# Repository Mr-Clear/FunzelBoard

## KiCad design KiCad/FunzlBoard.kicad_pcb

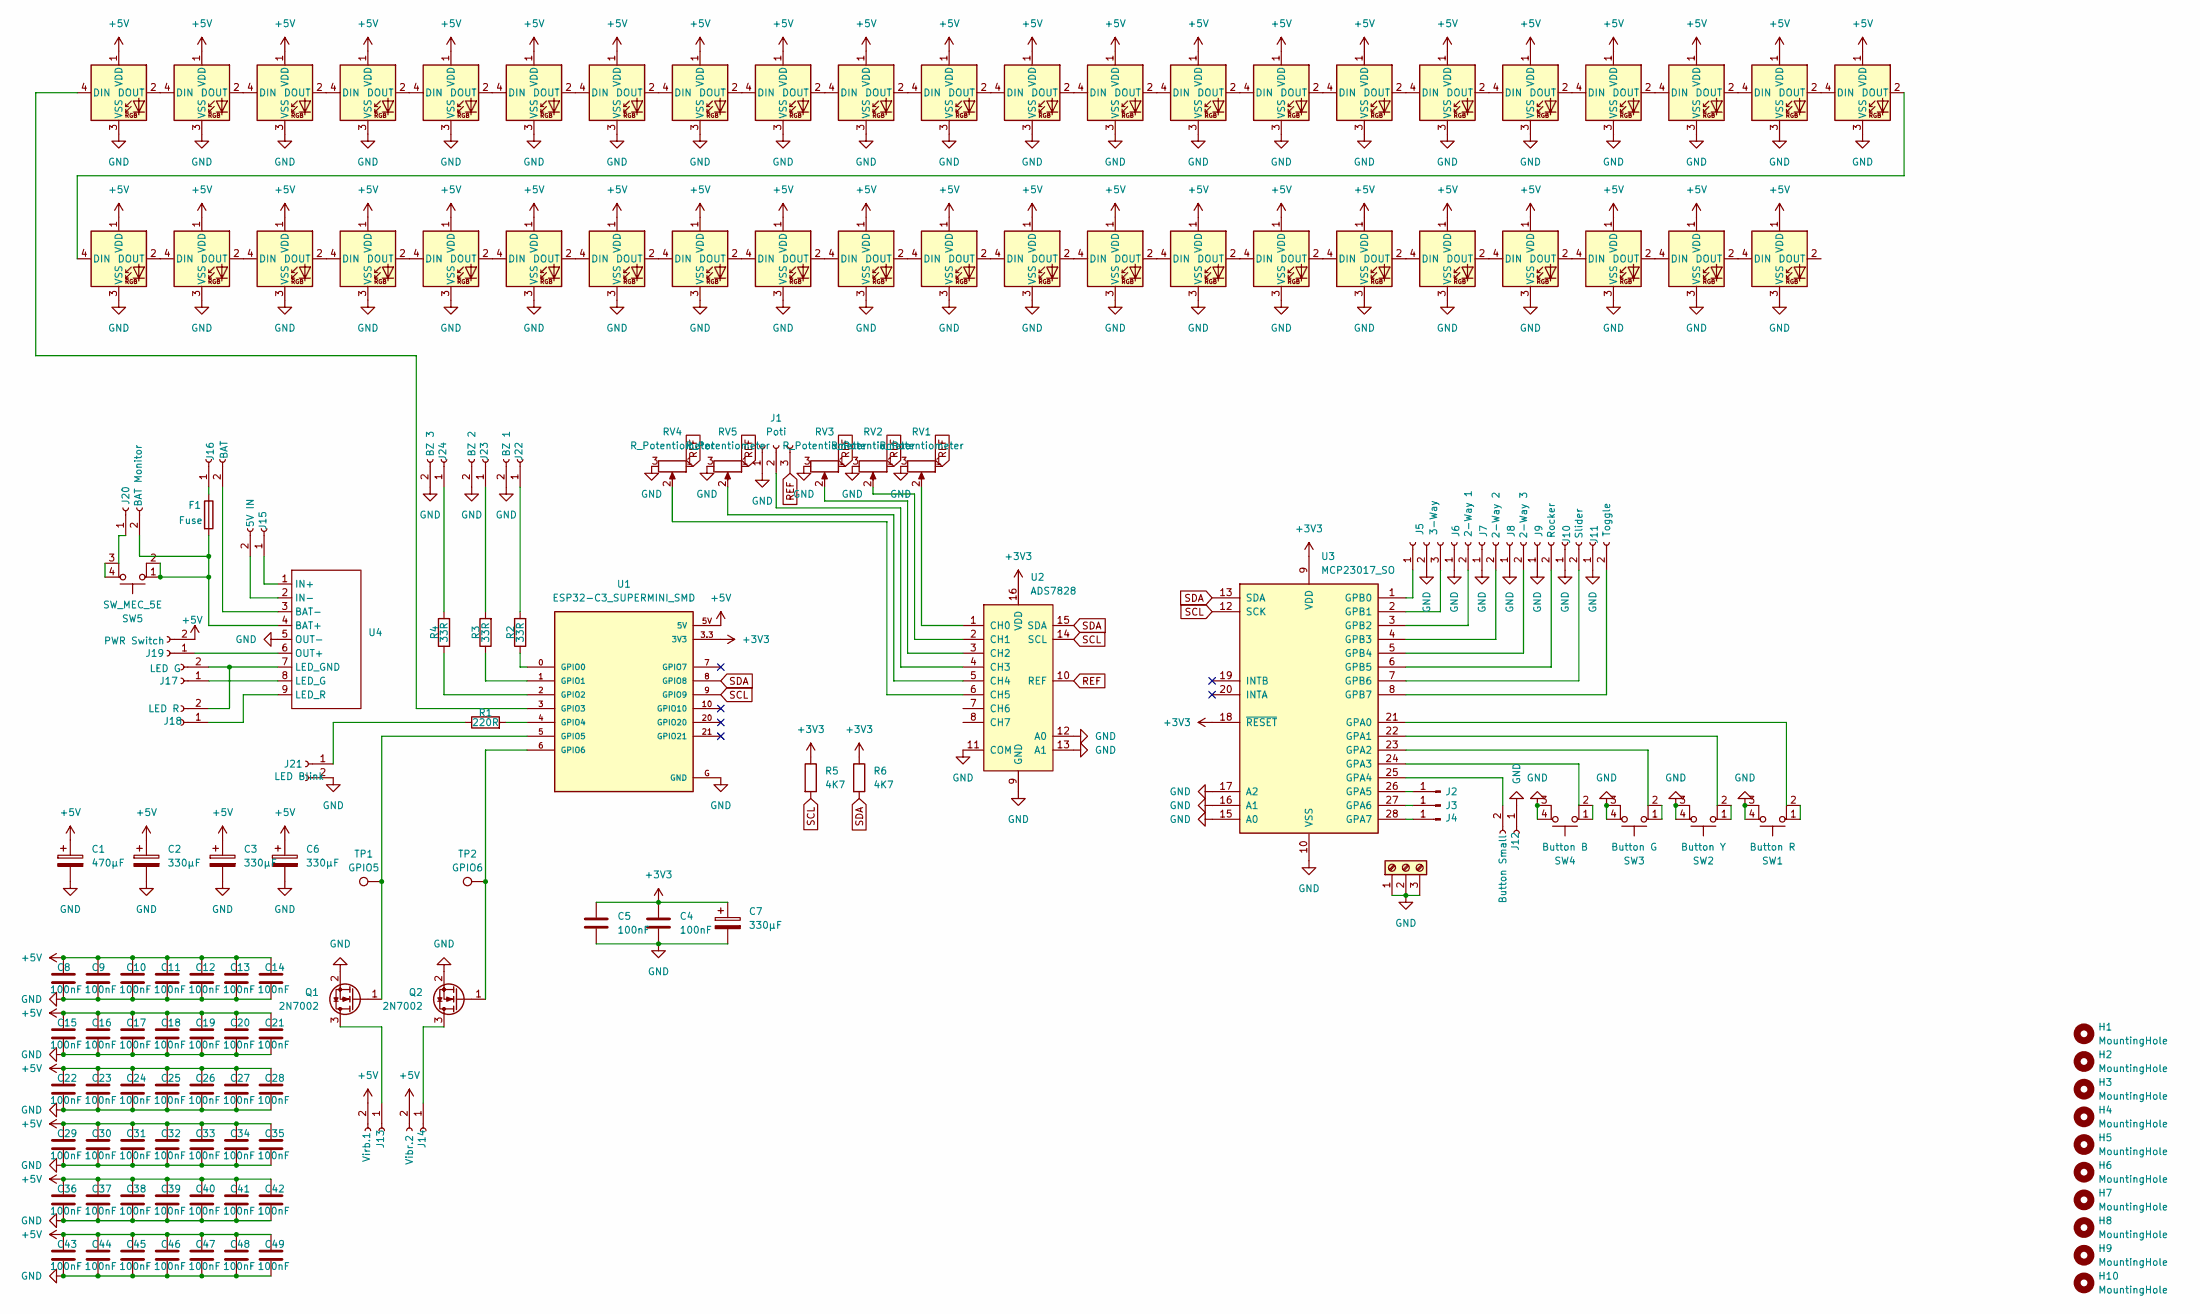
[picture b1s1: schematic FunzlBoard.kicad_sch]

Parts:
1WI1: Banana Plug Cable; TerminalBlock_Phoenix_MPT-0,5-3-2.54_1x03_P2.54mm_Horizontal
C1: 470µF; CP_Radial_D6.3mm_P2.50mm
C2, C3, C6, C7: 330µF; CP_Radial_D6.3mm_P2.50mm
C4, C5, C8, C9, C10, C11, C12, C13, C14, C15, C16, C17, C18, C19, C20, C21, C22, C23, C24, C25, C26, C27, C28, C29, C30, C31, C32, C33, C34, C35, C36, C37, C38, C39, C40, C41, C42, C43, C44, C45, C46, C47, C48, C49: 100nF; C_1206_3216Metric
D1, D2, D3, D4, D5, D6, D7, D8, D9, D10, D11, D12, D13, D14, D15, D16, D17, D18, D19, D20, D21, D22, D23, D24, D25, D26, D27, D28, D29, D30, D31, D32, D33, D34, D35, D36, D37, D38, D39, D40, D41, D42, D43: WS2812B; LED_WS2812B_PLCC4_5.0x5.0mm_P3.2mm
F1: Fuse; Fuseholder_Clip-5x20mm_Littelfuse_111_Inline_P20.00x5.00mm_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
H1, H2, H3, H4, H5, H6, H7, H8, H9, H10: MountingHole; MountingHole_4.3mm_M4_DIN965
J1: Poti; Connector3
J2: Banana Plug Socket 1; PinHeader_1x01_P2.54mm_Horizontal
J3: Banana Plug Socket 2; PinHeader_1x01_P2.54mm_Horizontal
J4: Banana Plug Socket 3; PinHeader_1x01_P2.54mm_Horizontal
J5: 3-Way; Connector3
J6: 2-Way 1; Connector2
J7: 2-Way 2; Connector2
J8: 2-Way 3; Connector2
J9: Rocker; Connector2
J10: Slider; Connector2
J11: Toggle; Connector2
J12: Button Small; Connector2
J13: Virb.1; Connector2
J14: Vibr.2; Connector2
J15: 5V IN; Connector2
J16: BAT; Connector2
J17: LED G; Connector2
J18: LED R; Connector2
J19: PWR Switch; Connector2
J20: BAT Monitor; Connector2
J21: LED Blink; Connector2
J22: BZ 1; Connector2
J23: BZ 2; Connector2
J24: BZ 3; Connector2
Q1, Q2: 2N7002; SOT-23
R1: 220R; R_1206_3216Metric
R2, R3, R4: 33R; R_1206_3216Metric
R5, R6: 4K7; R_1206_3216Metric
RV1, RV2, RV3: R_Potentiometer; Slider
RV4, RV5: R_Potentiometer; TrimmerH
SW1: Button R; ColorButton
SW2: Button Y; ColorButton
SW3: Button G; ColorButton
SW4: Button B; ColorButton
SW5: SW_MEC_5E; SW_PUSH_6mm_H13mm
TP1: GPIO5; TestPoint_THTPad_D1.5mm_Drill0.7mm
TP2: GPIO6; TestPoint_THTPad_D1.5mm_Drill0.7mm
U1: ESP32-C3_SUPERMINI_SMD; MODULE_ESP32-C3_SUPERMINI
U2: ADS7828; TSSOP-16_4.4x5mm_P0.65mm
U3: MCP23017_SO; SOIC-28W_7.5x17.9mm_P1.27mm
U4: Battery_Management

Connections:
+3V3: C4.1, C5.1, C7.1, R5.1, R6.1, U1.3.3 (3V3), U2.16 (VDD), U3.9 (VDD), U3.18 (~RESET)
+5V: C1.1, C2.1, C3.1, C6.1, C8.1, C9.1, C10.1, C11.1, C12.1, C13.1, C14.1, C15.1, C16.1, C17.1, C18.1, C19.1, C20.1, C21.1, C22.1, C23.1, C24.1, C25.1, C26.1, C27.1, C28.1, C29.1, C30.1, C31.1, C32.1, C33.1, C34.1, C35.1, C36.1, C37.1, C38.1, C39.1, C40.1, C41.1, C42.1, C43.1, C44.1, C45.1, C46.1, C47.1, C48.1, C49.1, D1.1 (VDD), D2.1 (VDD), D3.1 (VDD), D4.1 (VDD), D5.1 (VDD), D6.1 (VDD), D7.1 (VDD), D8.1 (VDD), D9.1 (VDD), D10.1 (VDD), D11.1 (VDD), D12.1 (VDD), D13.1 (VDD), D14.1 (VDD), D15.1 (VDD), D16.1 (VDD), D17.1 (VDD), D18.1 (VDD), D19.1 (VDD), D20.1 (VDD), D21.1 (VDD), D22.1 (VDD), D23.1 (VDD), D24.1 (VDD), D25.1 (VDD), D26.1 (VDD), D27.1 (VDD), D28.1 (VDD), D29.1 (VDD), D30.1 (VDD), D31.1 (VDD), D32.1 (VDD), D33.1 (VDD), D34.1 (VDD), D35.1 (VDD), D36.1 (VDD), D37.1 (VDD), D38.1 (VDD), D39.1 (VDD), D40.1 (VDD), D41.1 (VDD), D42.1 (VDD), D43.1 (VDD), J13.2, J14.2, J19.2, U1.5V
GND: 1WI1.1 (GND), 1WI1.2 (GND), 1WI1.3 (GND), C1.2, C2.2, C3.2, C4.2, C5.2, C6.2, C7.2, C8.2, C9.2, C10.2, C11.2, C12.2, C13.2, C14.2, C15.2, C16.2, C17.2, C18.2, C19.2, C20.2, C21.2, C22.2, C23.2, C24.2, C25.2, C26.2, C27.2, C28.2, C29.2, C30.2, C31.2, C32.2, C33.2, C34.2, C35.2, C36.2, C37.2, C38.2, C39.2, C40.2, C41.2, C42.2, C43.2, C44.2, C45.2, C46.2, C47.2, C48.2, C49.2, D1.3 (VSS), D2.3 (VSS), D3.3 (VSS), D4.3 (VSS), D5.3 (VSS), D6.3 (VSS), D7.3 (VSS), D8.3 (VSS), D9.3 (VSS), D10.3 (VSS), D11.3 (VSS), D12.3 (VSS), D13.3 (VSS), D14.3 (VSS), D15.3 (VSS), D16.3 (VSS), D17.3 (VSS), D18.3 (VSS), D19.3 (VSS), D20.3 (VSS), D21.3 (VSS), D22.3 (VSS), D23.3 (VSS), D24.3 (VSS), D25.3 (VSS), D26.3 (VSS), D27.3 (VSS), D28.3 (VSS), D29.3 (VSS), D30.3 (VSS), D31.3 (VSS), D32.3 (VSS), D33.3 (VSS), D34.3 (VSS), D35.3 (VSS), D36.3 (VSS), D37.3 (VSS), D38.3 (VSS), D39.3 (VSS), D40.3 (VSS), D41.3 (VSS), D42.3 (VSS), D43.3 (VSS), J1.1, J5.2, J6.1, J7.1, J8.1, J9.1, J10.1, J11.1, J12.1, J21.2, J22.2, J23.2, J24.2, Q1.2 (S), Q2.2 (S), RV1.3, RV2.3, RV3.3, RV4.3, RV5.3, SW1.3 (K), SW1.4 (A), SW2.3 (K), SW2.4 (A), SW3.3 (K), SW3.4 (A), SW4.3 (K), SW4.4 (A), U1.G (GND), U2.9 (GND), U2.11 (COM), U2.12 (A0), U2.13 (A1), U3.10 (VSS), U3.15 (A0), U3.16 (A1), U3.17 (A2), U4.5 (OUT-)
unnamed: D1.4 (DIN), U1.3 (GPIO3)
unnamed: D1.2 (DOUT), D2.4 (DIN)
unnamed: D2.2 (DOUT), D3.4 (DIN)
unnamed: D3.2 (DOUT), D4.4 (DIN)
unnamed: D4.2 (DOUT), D5.4 (DIN)
unnamed: D5.2 (DOUT), D6.4 (DIN)
unnamed: D6.2 (DOUT), D7.4 (DIN)
unnamed: D7.2 (DOUT), D8.4 (DIN)
unnamed: D8.2 (DOUT), D9.4 (DIN)
unnamed: D9.2 (DOUT), D10.4 (DIN)
unnamed: D10.2 (DOUT), D11.4 (DIN)
unnamed: D11.2 (DOUT), D12.4 (DIN)
unnamed: D12.2 (DOUT), D13.4 (DIN)
unnamed: D13.2 (DOUT), D14.4 (DIN)
unnamed: D14.2 (DOUT), D15.4 (DIN)
unnamed: D15.2 (DOUT), D16.4 (DIN)
unnamed: D16.2 (DOUT), D17.4 (DIN)
unnamed: D17.2 (DOUT), D18.4 (DIN)
unnamed: D18.2 (DOUT), D19.4 (DIN)
unnamed: D19.2 (DOUT), D20.4 (DIN)
unnamed: D20.2 (DOUT), D21.4 (DIN)
unnamed: D21.2 (DOUT), D22.4 (DIN)
unnamed: D22.2 (DOUT), D23.4 (DIN)
unnamed: D23.2 (DOUT), D24.4 (DIN)
unnamed: D24.2 (DOUT), D25.4 (DIN)
unnamed: D25.2 (DOUT), D26.4 (DIN)
unnamed: D26.2 (DOUT), D27.4 (DIN)
unnamed: D27.2 (DOUT), D28.4 (DIN)
unnamed: D28.2 (DOUT), D29.4 (DIN)
unnamed: D29.2 (DOUT), D30.4 (DIN)
unnamed: D30.2 (DOUT), D31.4 (DIN)
unnamed: D31.2 (DOUT), D32.4 (DIN)
unnamed: D32.2 (DOUT), D33.4 (DIN)
unnamed: D33.2 (DOUT), D34.4 (DIN)
unnamed: D34.2 (DOUT), D35.4 (DIN)
unnamed: D35.2 (DOUT), D36.4 (DIN)
unnamed: D36.2 (DOUT), D37.4 (DIN)
unnamed: D37.2 (DOUT), D38.4 (DIN)
unnamed: D38.2 (DOUT), D39.4 (DIN)
unnamed: D39.2 (DOUT), D40.4 (DIN)
unnamed: D40.2 (DOUT), D41.4 (DIN)
unnamed: D41.2 (DOUT), D42.4 (DIN)
unnamed: D42.2 (DOUT), D43.4 (DIN)
unnamed: J1.2, U2.4 (CH3)
unnamed: J2.1, U3.26 (GPA5)
unnamed: J3.1, U3.27 (GPA6)
unnamed: J4.1, U3.28 (GPA7)
unnamed: J5.1, U3.1 (GPB0)
unnamed: J5.3, U3.2 (GPB1)
unnamed: J6.2, U3.3 (GPB2)
unnamed: J7.2, U3.4 (GPB3)
unnamed: J8.2, U3.5 (GPB4)
unnamed: J9.2, U3.6 (GPB5)
unnamed: J10.2, U3.7 (GPB6)
unnamed: J11.2, U3.8 (GPB7)
unnamed: J12.2, U3.25 (GPA4)
unnamed: J13.1, Q1.3 (D)
unnamed: J14.1, Q2.3 (D)
unnamed: J15.1, U4.1 (IN+)
unnamed: J15.2, U4.2 (IN-)
unnamed: F1.1, J16.1
unnamed: J16.2, U4.3 (BAT-)
unnamed: J17.1, U4.8 (LED_G)
unnamed: J17.2, J18.2, U4.7 (LED_GND)
unnamed: J18.1, U4.9 (LED_R)
unnamed: J19.1, U4.6 (OUT+)
unnamed: F1.2, J20.2, SW5.1, SW5.2, U4.4 (BAT+)
unnamed: J21.1, R1.1
unnamed: J22.1, R2.2
unnamed: J23.1, R3.2
unnamed: J24.1, R4.2
unnamed: Q1.1 (G), TP1.1, U1.5 (GPIO5)
unnamed: Q2.1 (G), TP2.1, U1.6 (GPIO6)
unnamed: SW1.1, SW1.2
unnamed: SW2.1, SW2.2
unnamed: SW3.1, SW3.2
unnamed: SW4.1, SW4.2
unnamed: SW5.3 (K), SW5.4 (A)
unnamed: R2.1, U1.0 (GPIO0)
unnamed: R3.1, U1.1 (GPIO1)
unnamed: R4.1, U1.2 (GPIO2)
unnamed: R1.2, U1.4 (GPIO4)
unnamed: RV1.2, U2.1 (CH0)
unnamed: RV2.2, U2.2 (CH1)
unnamed: RV3.2, U2.3 (CH2)
unnamed: RV5.2, U2.5 (CH4)
unnamed: RV4.2, U2.6 (CH5)
REF: J1.3, RV1.1, RV2.1, RV3.1, RV4.1, RV5.1, U2.10 (REF)
SCL: R5.2, U1.9 (GPIO9), U2.14 (SCL), U3.12 (SCK)
SDA: R6.2, U1.8 (GPIO8), U2.15 (SDA), U3.13 (SDA)

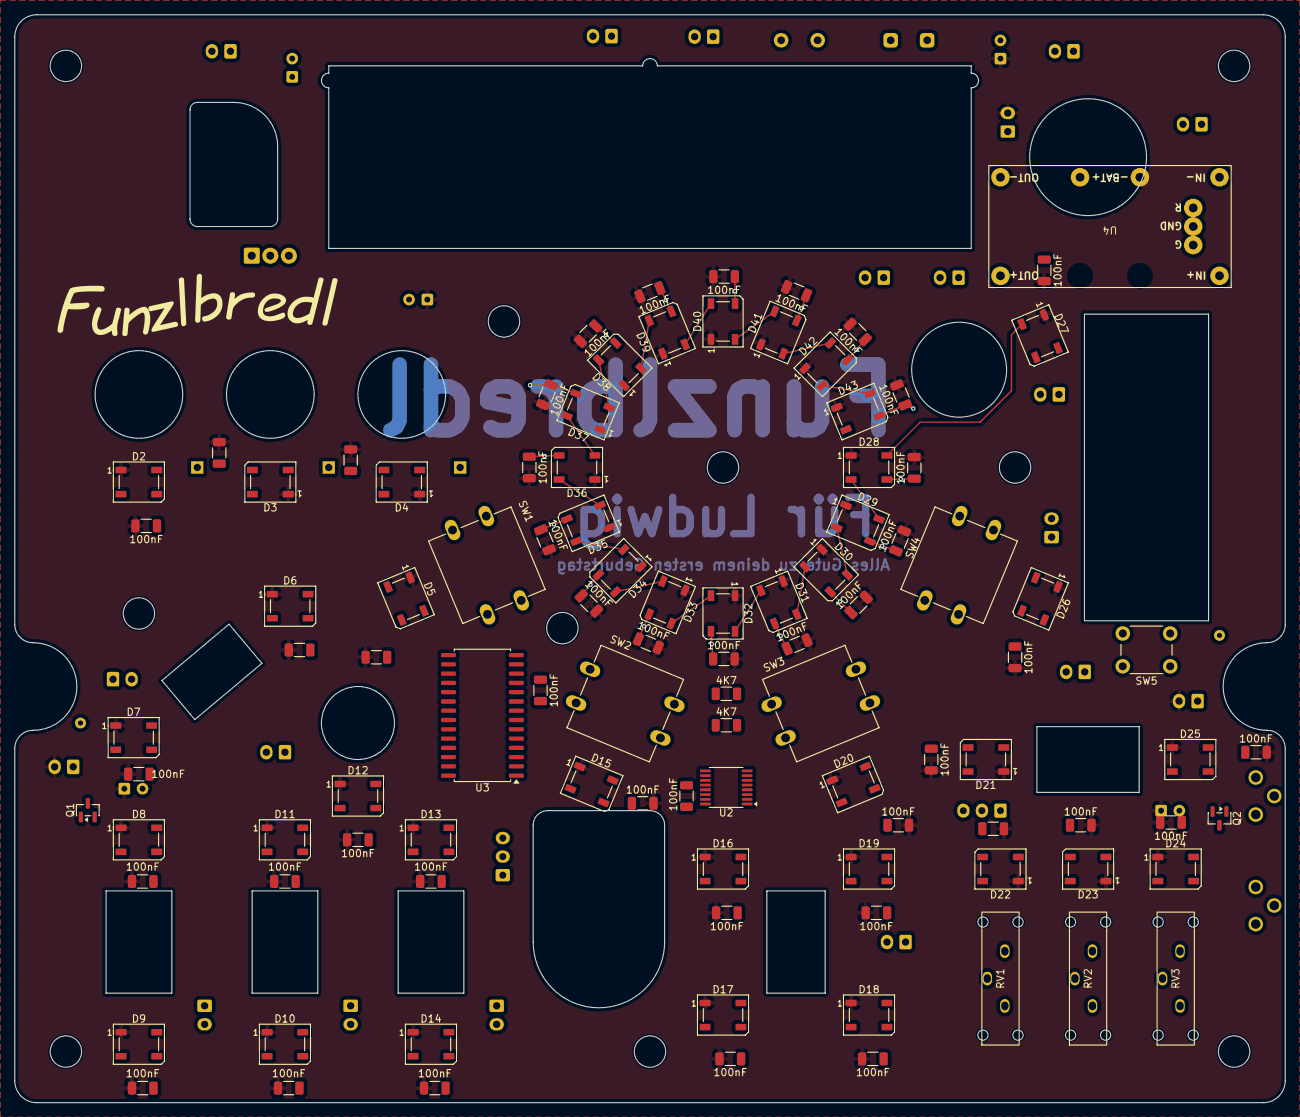
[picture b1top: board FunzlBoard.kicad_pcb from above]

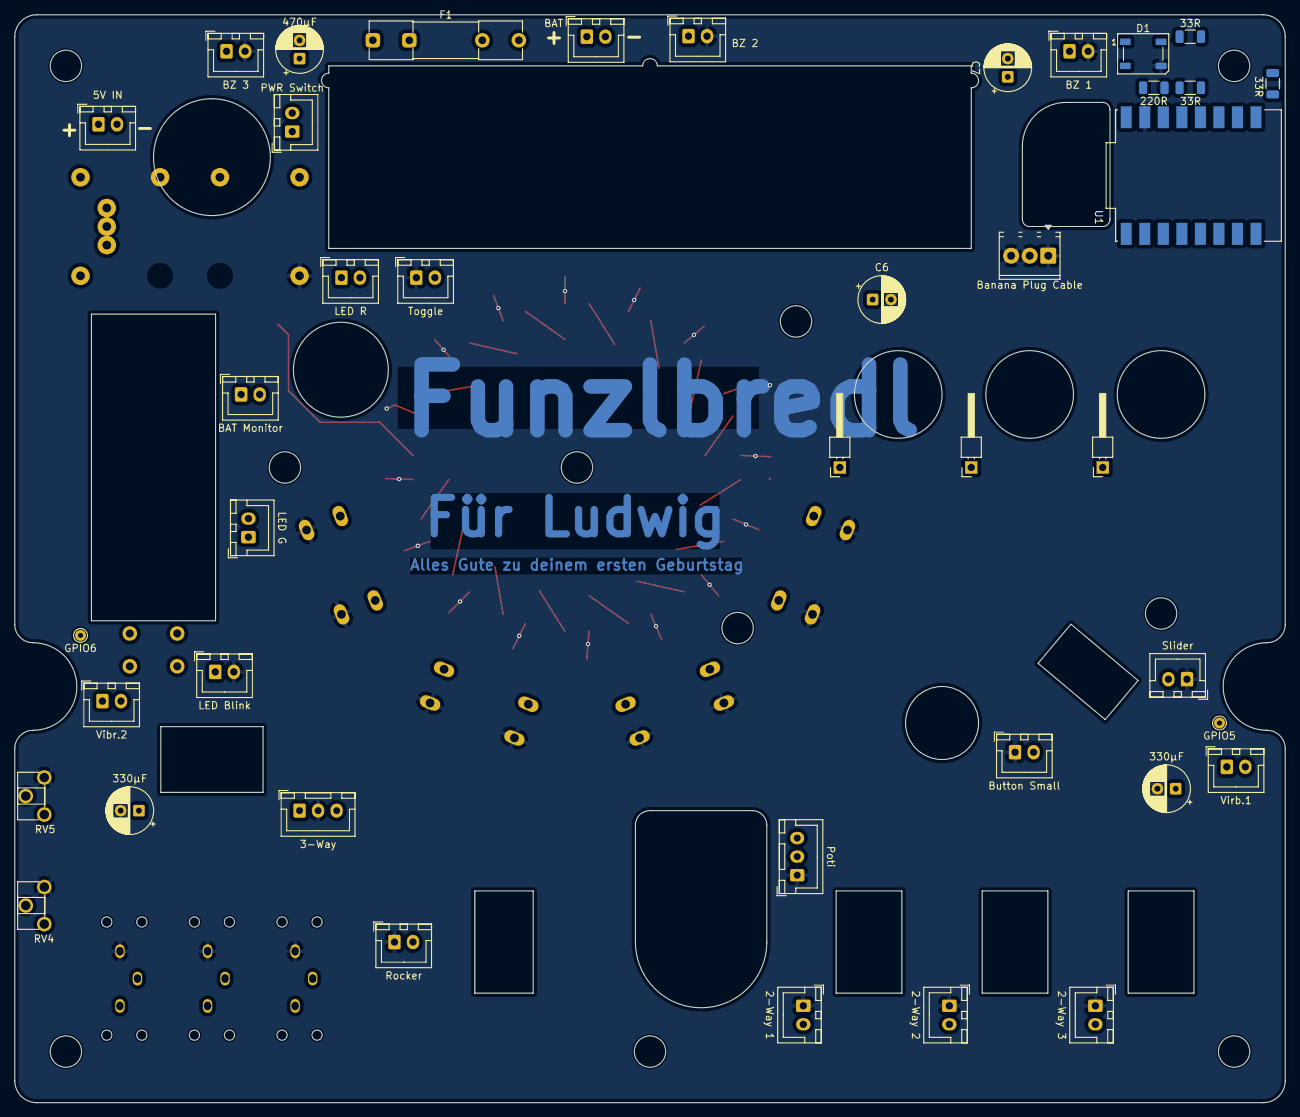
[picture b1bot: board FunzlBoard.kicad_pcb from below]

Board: 2 copper layers, 174.0 x 149.0 mm, 152 parts (41 on the bottom side), 93 nets.

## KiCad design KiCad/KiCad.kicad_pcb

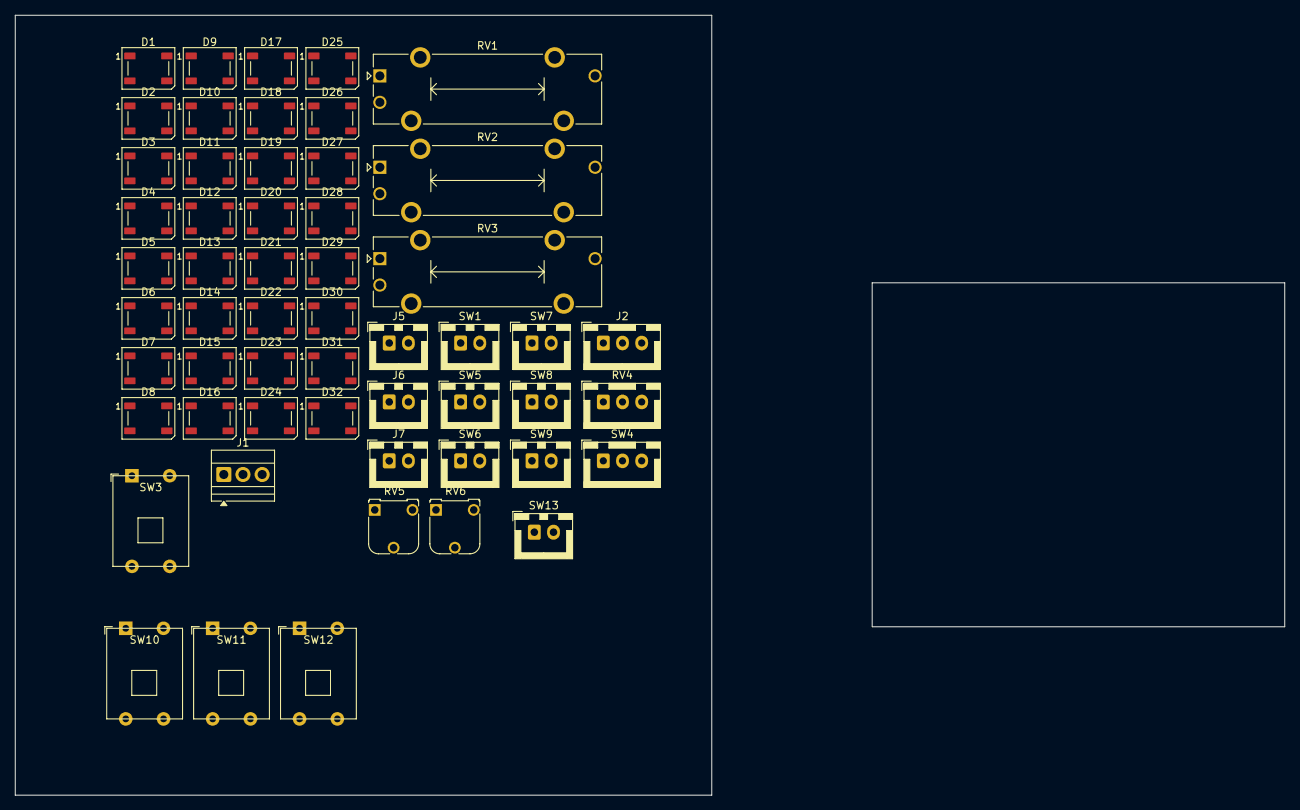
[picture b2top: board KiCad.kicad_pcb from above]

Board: 2 copper layers, 92.2 x 103.3 mm, 55 parts (0 on the bottom side), 40 nets, no tracks yet.

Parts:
D1, D2, D3, D4, D5, D6, D7, D8, D9, D10, D11, D12, D13, D14, D15, D16, D17, D18, D19, D20, D21, D22, D23, D24, D25, D26, D27, D28, D29, D30, D31, D32: WS2812B; LED_WS2812B_PLCC4_5.0x5.0mm_P3.2mm
J1: Socket Line; TerminalBlock_Xinya_XY308-2.54-3P_1x03_P2.54mm_Horizontal
J2: Sockets; XH-3A
J5: Battery; XH-2A
J6: USB; XH-2A
J7: Battery Indicator; XH-2A
RV1: Slider Blue; Potentiometer_Bourns_PTA1543_Single_Slide
RV2: Slider Green; Potentiometer_Bourns_PTA1543_Single_Slide
RV3: Slider Red; Potentiometer_Bourns_PTA1543_Single_Slide
RV4: Main Potentiometer; XH-3A
RV5: Setting Potentiometer 2; Potentiometer_Runtron_RM-065_Vertical
RV6: Setting Potentiometer 1; Potentiometer_Runtron_RM-065_Vertical
SW1: Toggle Red; XH-2A
SW3: Button Red; Switch THT
SW4: SW_SPDT_MSM; XH-3A
SW5: Toggle Green; XH-2A
SW6: Toggle Blue; XH-2A
SW7, SW8: SW_SPDT; XH-2A
SW9: SW_SPST; XH-2A
SW10: Button Green; Switch THT
SW11: Button Blue; Switch THT
SW12: Button Yellow; Switch THT
SW13: Button Small; XH-2A

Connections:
+5V: D1.3 (VSS), D2.3 (VSS), D3.3 (VSS), D4.3 (VSS), D5.3 (VSS), D6.3 (VSS), D7.3 (VSS), D8.3 (VSS), D9.3 (VSS), D10.3 (VSS), D11.3 (VSS), D12.3 (VSS), D13.3 (VSS), D14.3 (VSS), D15.3 (VSS), D16.3 (VSS), D17.3 (VSS), D18.3 (VSS), D19.3 (VSS), D20.3 (VSS), D21.3 (VSS), D22.3 (VSS), D23.3 (VSS), D24.3 (VSS), D25.3 (VSS), D26.3 (VSS), D27.3 (VSS), D28.3 (VSS), D29.3 (VSS), D30.3 (VSS), D31.3 (VSS), D32.3 (VSS), SW3.1 (A), SW3.2 (A)
+BATT: J5.1, J7.1
ADC-Hi: RV1.1, RV2.1, RV3.1, RV4.1, RV5.1, RV6.1
ADC_Lo: RV1.3, RV2.3, RV3.3, RV4.3, RV5.3, RV6.3
GND: D1.1 (VDD), D2.1 (VDD), D3.1 (VDD), D4.1 (VDD), D5.1 (VDD), D6.1 (VDD), D7.1 (VDD), D8.1 (VDD), D9.1 (VDD), D10.1 (VDD), D11.1 (VDD), D12.1 (VDD), D13.1 (VDD), D14.1 (VDD), D15.1 (VDD), D16.1 (VDD), D17.1 (VDD), D18.1 (VDD), D19.1 (VDD), D20.1 (VDD), D21.1 (VDD), D22.1 (VDD), D23.1 (VDD), D24.1 (VDD), D25.1 (VDD), D26.1 (VDD), D27.1 (VDD), D28.1 (VDD), D29.1 (VDD), D30.1 (VDD), D31.1 (VDD), D32.1 (VDD), J1.1, J1.2, J1.3, J5.2, J6.2, SW3.3 (B), SW3.4 (B), SW4.1, SW4.3 (4), SW9.2 (B), SW10.3 (B), SW10.4 (B), SW11.3 (B), SW11.4 (B), SW12.3 (B), SW12.4 (B)
unnamed: D1.2 (DOUT), D2.4 (DIN)
unnamed: D2.2 (DOUT), D3.4 (DIN)
unnamed: D3.2 (DOUT), D4.4 (DIN)
unnamed: D4.2 (DOUT), D5.4 (DIN)
unnamed: D5.2 (DOUT), D6.4 (DIN)
unnamed: D6.2 (DOUT), D7.4 (DIN)
unnamed: D7.2 (DOUT), D8.4 (DIN)
unnamed: D8.2 (DOUT), D9.4 (DIN)
unnamed: D9.2 (DOUT), D10.4 (DIN)
unnamed: D10.2 (DOUT), D11.4 (DIN)
unnamed: D11.2 (DOUT), D12.4 (DIN)
unnamed: D12.2 (DOUT), D13.4 (DIN)
unnamed: D13.2 (DOUT), D14.4 (DIN)
unnamed: D14.2 (DOUT), D15.4 (DIN)
unnamed: D15.2 (DOUT), D16.4 (DIN)
unnamed: D16.2 (DOUT), D17.4 (DIN)
unnamed: D17.2 (DOUT), D19.4 (DIN)
unnamed: D18.4 (DIN), D31.2 (DOUT)
unnamed: D18.2 (DOUT), D20.4 (DIN)
unnamed: D19.2 (DOUT), D21.4 (DIN)
unnamed: D20.2 (DOUT), D22.4 (DIN)
unnamed: D21.2 (DOUT), D23.4 (DIN)
unnamed: D22.2 (DOUT), D24.4 (DIN)
unnamed: D23.2 (DOUT), D25.4 (DIN)
unnamed: D24.2 (DOUT), D26.4 (DIN)
unnamed: D25.2 (DOUT), D27.4 (DIN)
unnamed: D26.2 (DOUT), D28.4 (DIN)
unnamed: D27.2 (DOUT), D29.4 (DIN)
unnamed: D28.2 (DOUT), D30.4 (DIN)
unnamed: D29.2 (DOUT), D31.4 (DIN)
unnamed: D30.2 (DOUT), D32.4 (DIN)
unnamed: SW10.1 (A), SW10.2 (A)
unnamed: SW11.1 (A), SW11.2 (A)
unnamed: SW12.1 (A), SW12.2 (A)
unnamed: SW13.1 (A), SW13.2 (A)

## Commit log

2025-10-14 Read ADC values
2025-10-14 Take commands by serial
2025-10-14 Scan I2C on command
2025-10-17 Read button states
2025-10-17 Add WS2812B output
2025-10-18 Add buzzers
2025-10-18 Add seperate logic file
2025-10-19 Add Slider Knob
2025-10-19 Show sound circle
2025-10-19 Drive motor
2025-10-19 Put logic into action classes
2025-10-19 Option to disable serial output
2025-10-19 Don't clear pixels
2025-10-19 Replace Action classes by plain functions
2025-10-19 Add scheduler
2025-10-20 Add state machine
2025-10-20 Pith tone in octaves
2025-10-20 Panic mode
2025-10-20 Color mix
2025-10-22 Use 3 buzzers
2025-10-22 Add music player
2025-10-22 Play music from serial
2025-10-23 Rewrote musicPlayer for a much simpler data format
2025-10-24 Start implementing Song Editor
2025-10-24 Hover track
2025-10-25 Show tracks and notes
2025-10-25 Clean up
2025-10-25 Save and load config
2025-10-25 Select notes
2025-10-25 Frame select notes
2025-10-26 Indicate buzzer with fill color
2025-10-26 Set buzzer of selected notes
2025-10-26 Edit track title
2025-10-26 Move track up/down
2025-10-26 Select all notes in track
2025-10-26 Highlight track and note
2025-10-26 Show details in left docks
2025-10-26 Show nodes in QTableView
2025-10-26 Save and load file
2025-10-26 Calculate overlapping notes
2025-10-26 Send notes to FunzlBoard
2025-10-27 Play song
2025-10-27 Fix timing
2025-10-28 Change song format to binary
2025-11-02 Add debug putput for MCP23017 config
2025-11-02 Replace ADS1115 by ADS7828
2025-11-02 Add KiCad project
2025-11-02 Add LED cap
2025-11-02 Normalize ADC readings
2025-11-04 Turn poti order
2025-11-04 Color float on button press
2025-11-04 Create 3d model
2025-11-04 Restart KiCad project
2025-11-04 Add main screw holes
2025-11-04 Show mainboard in OpenSCAD
2025-11-07 Cut out for battery
2025-11-14 Use sleeve in led cap
2025-11-14 Chacnge pin layout to 16-Pin Super Mini
2025-11-14 Align LEDs on main board
2025-11-15 Add main screws
2025-11-15 Add screws to mount components
2025-11-15 Cut out board for components
2025-11-15 Add Color Buttons to PCB
2025-11-15 Add footprints for sliders
2025-11-15 Add DIP Switch to PCB
2025-11-15 Add slider footprint
2025-11-16 Move a screw
2025-11-16 Add Trimmer
2025-11-16 Fix motor pin
2025-11-16 Add trimmer and vibrators
2025-11-16 Support 2 vibrators
2025-11-16 Add connectors
2025-11-17 Add 2nd trimmer
2025-11-17 Add Battery Management to OpenSCAD
2025-11-17 Place capas
2025-11-17 Add fuse
2025-11-17 Make space for battery
2025-11-17 Add screws for battery indicator
